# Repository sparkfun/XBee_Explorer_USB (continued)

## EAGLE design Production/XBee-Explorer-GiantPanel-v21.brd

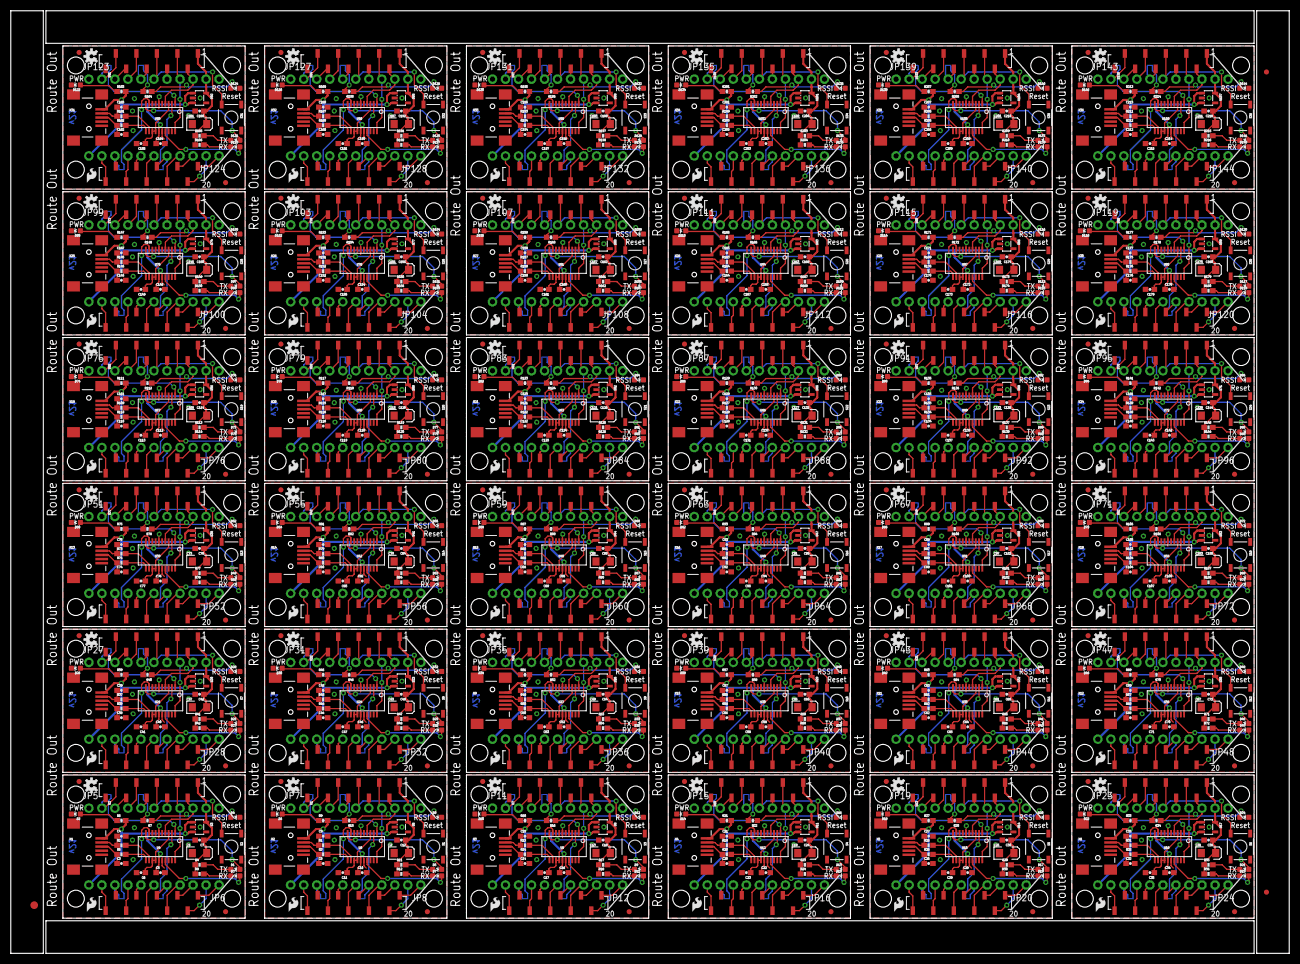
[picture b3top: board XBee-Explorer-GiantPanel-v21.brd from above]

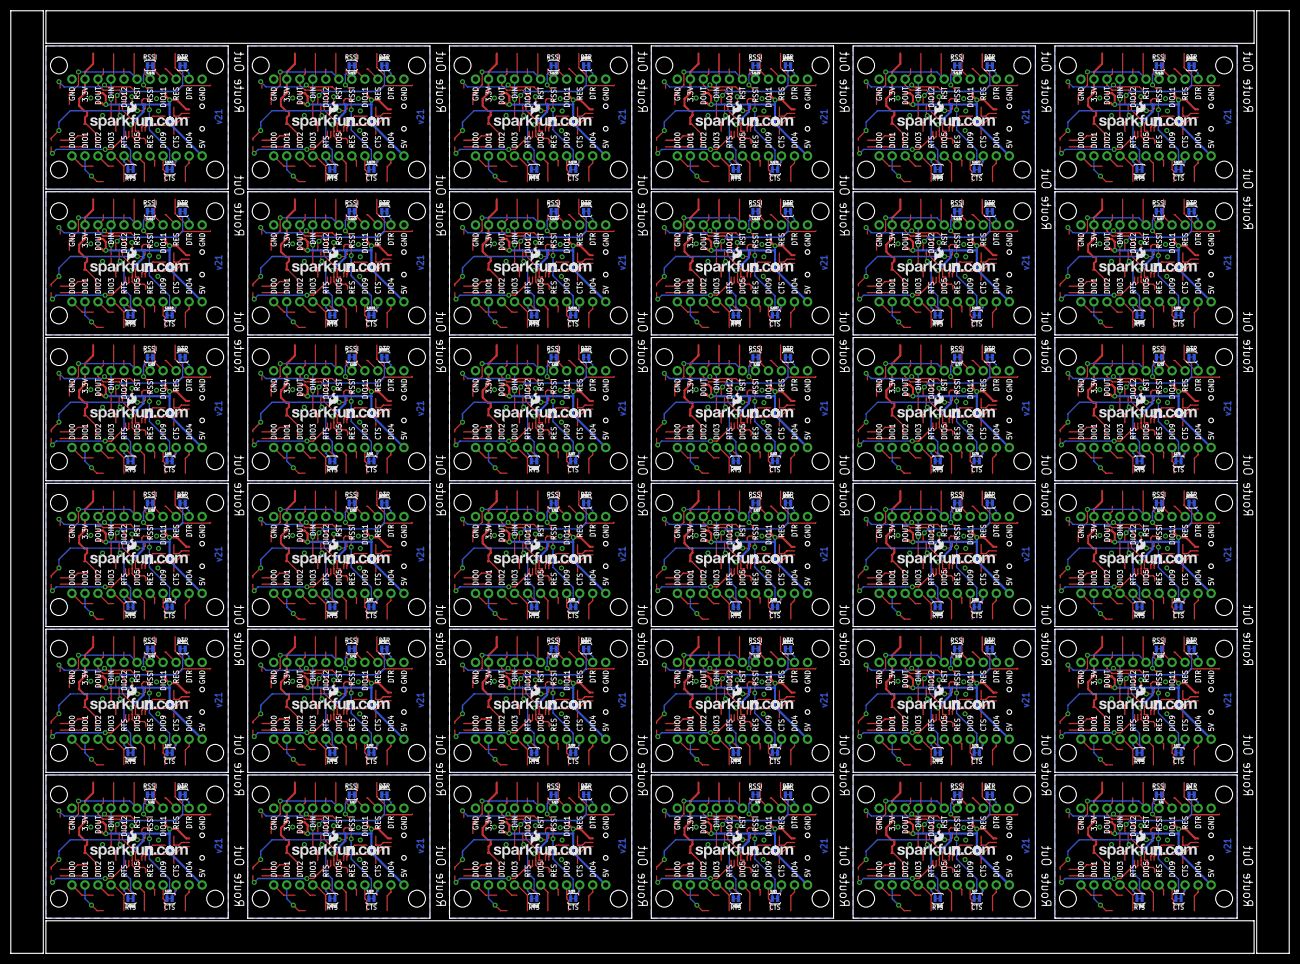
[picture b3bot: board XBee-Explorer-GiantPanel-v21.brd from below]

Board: 2 copper layers, 249.4 x 183.9 mm, 1299 parts (180 on the bottom side), 1296 nets.

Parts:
C1, C2, C13, C19, C25, C31, C37, C43, C49, C55, C61, C67, C73, C79, C85, C91, C97, C103, C109, C115, C121, C127, C133, C139, C145, C151, C157, C163, C169, C175, C181, C187, C193, C199, C205, C211: 10uF; EIA3216
C3, C4, C8, C9, C14, C15, C20, C21, C26, C27, C32, C33, C38, C39, C44, C45, C50, C51, C56, C57, C62, C63, C68, C69, C74, C75, C80, C81, C86, C87, C92, C93, C98, C99, C104, C105, C110, C111, C116, C117, C122, C123, C128, C129, C134, C135, C140, C141, C146, C147, C152, C153, C158, C159, C164, C165, C170, C171, C176, C177, C182, C183, C188, C189, C194, C195, C200, C201, C206, C207, C212, C213: 47pF; 0603-CAP
C5, C6, C7, C10, C11, C12, C16, C17, C18, C22, C23, C24, C28, C29, C30, C34, C35, C36, C40, C41, C42, C46, C47, C48, C52, C53, C54, C58, C59, C60, C64, C65, C66, C70, C71, C72, C76, C77, C78, C82, C83, C84, C88, C89, C90, C94, C95, C96, C100, C101, C102, C106, C107, C108, C112, C113, C114, C118, C119, C120, C124, C125, C126, C130, C131, C132, C136, C137, C138, C142, C143, C144, C148, C149, C150, C154, C155, C156, C160, C161, C162, C166, C167, C168, C172, C173, C174, C178, C179, C180, C184, C185, C186, C190, C191, C192, C196, C197, C198, C202, C203, C204, C208, C209, C210, C214, C215, C216: 0.1uF; 0603-CAP
D1, D2, D5, D6, D9, D10, D13, D14, D17, D18, D21, D22, D25, D26, D29, D30, D33, D34, D37, D38, D41, D42, D45, D46, D49, D50, D53, D54, D57, D58, D61, D62, D65, D66, D69, D70, D73, D74, D77, D78, D81, D82, D85, D86, D89, D90, D93, D94, D97, D98, D101, D102, D105, D106, D109, D110, D113, D114, D117, D118, D121, D122, D125, D126, D129, D130, D133, D134, D137, D138, D141, D142: RED; LED-0603
D3, D4, D7, D8, D11, D12, D15, D16, D19, D20, D23, D24, D27, D28, D31, D32, D35, D36, D39, D40, D43, D44, D47, D48, D51, D52, D55, D56, D59, D60, D63, D64, D67, D68, D71, D72, D75, D76, D79, D80, D83, D84, D87, D88, D91, D92, D95, D96, D99, D100, D103, D104, D107, D108, D111, D112, D115, D116, D119, D120, D123, D124, D127, D128, D131, D132, D135, D136, D139, D140, D143, D144: GREEN; LED-0603
E$1: FIDUCIAL-1.5X3
E$5, E$7: FIDUCIAL-1X2
JP1, JP2, JP3, JP4, JP9, JP10, JP13, JP14, JP17, JP18, JP21, JP22, JP25, JP26, JP29, JP30, JP33, JP34, JP37, JP38, JP41, JP42, JP45, JP46, JP49, JP50, JP53, JP54, JP57, JP58, JP61, JP62, JP65, JP66, JP69, JP70, JP73, JP74, JP77, JP78, JP81, JP82, JP85, JP86, JP89, JP90, JP93, JP94, JP97, JP98, JP101, JP102, JP105, JP106, JP109, JP110, JP113, JP114, JP117, JP118, JP121, JP122, JP125, JP126, JP129, JP130, JP133, JP134, JP137, JP138, JP141, JP142: FIDUCIAL1X2; FIDUCIAL-1X2
JP5, JP6, JP7, JP8, JP11, JP12, JP15, JP16, JP19, JP20, JP23, JP24, JP27, JP28, JP31, JP32, JP35, JP36, JP39, JP40, JP43, JP44, JP47, JP48, JP51, JP52, JP55, JP56, JP59, JP60, JP63, JP64, JP67, JP68, JP71, JP72, JP75, JP76, JP79, JP80, JP83, JP84, JP87, JP88, JP91, JP92, JP95, JP96, JP99, JP100, JP103, JP104, JP107, JP108, JP111, JP112, JP115, JP116, JP119, JP120, JP123, JP124, JP127, JP128, JP131, JP132, JP135, JP136, JP139, JP140, JP143, JP144: M111X11_NO_SILK; 1X11_NO_SILK
LOGO1, LOGO2, LOGO3, LOGO4, LOGO5, LOGO6, LOGO7, LOGO8, LOGO9, LOGO10, LOGO11, LOGO12, LOGO13, LOGO14, LOGO15, LOGO16, LOGO17, LOGO18, LOGO19, LOGO20, LOGO21, LOGO22, LOGO23, LOGO24, LOGO25, LOGO26, LOGO27, LOGO28, LOGO29, LOGO30, LOGO31, LOGO32, LOGO33, LOGO34, LOGO35, LOGO36: OSHW-LOGOS; OSHW-LOGO-S
R1, R2, R3, R5, R13, R14, R19, R20, R25, R26, R31, R32, R37, R38, R43, R44, R49, R50, R55, R56, R61, R62, R67, R68, R73, R74, R79, R80, R85, R86, R91, R92, R97, R98, R103, R104, R109, R110, R115, R116, R121, R122, R127, R128, R133, R134, R139, R140, R145, R146, R151, R152, R157, R158, R163, R164, R169, R170, R175, R176, R181, R182, R187, R188, R193, R194, R199, R200, R205, R206, R211, R212: 27; 0603-RES
R4, R6, R8, R9, R11, R12, R15, R17, R18, R21, R23, R24, R27, R29, R30, R33, R35, R36, R39, R41, R42, R45, R47, R48, R51, R53, R54, R57, R59, R60, R63, R65, R66, R69, R71, R72, R75, R77, R78, R81, R83, R84, R87, R89, R90, R93, R95, R96, R99, R101, R102, R105, R107, R108, R111, R113, R114, R117, R119, R120, R123, R125, R126, R129, R131, R132, R135, R137, R138, R141, R143, R144, R147, R149, R150, R153, R155, R156, R159, R161, R162, R165, R167, R168, R171, R173, R174, R177, R179, R180, R183, R185, R186, R189, R191, R192, R195, R197, R198, R201, R203, R204, R207, R209, R210, R213, R215, R216: 1k; 0603-RES
R7, R10, R16, R22, R28, R34, R40, R46, R52, R58, R64, R70, R76, R82, R88, R94, R100, R106, R112, R118, R124, R130, R136, R142, R148, R154, R160, R166, R172, R178, R184, R190, R196, R202, R208, R214: 330; 0603-RES
S1, S2, S3, S4, S5, S6, S7, S8, S9, S10, S11, S12, S13, S14, S15, S16, S17, S18, S19, S20, S21, S22, S23, S24, S25, S26, S27, S28, S29, S30, S31, S32, S33, S34, S35, S36: Reset; TACTILE_SWITCH_SMD
SJ1, SJ5, SJ9, SJ13, SJ17, SJ21, SJ25, SJ29, SJ33, SJ37, SJ41, SJ45, SJ49, SJ53, SJ57, SJ61, SJ65, SJ69, SJ73, SJ77, SJ81, SJ85, SJ89, SJ93, SJ97, SJ101, SJ105, SJ109, SJ113, SJ117, SJ121, SJ125, SJ129, SJ133, SJ137, SJ141: RSSI_LED_EN; SJ_2S-TRACE
SJ2, SJ8, SJ12, SJ16, SJ20, SJ24, SJ28, SJ32, SJ36, SJ40, SJ44, SJ48, SJ52, SJ56, SJ60, SJ64, SJ68, SJ72, SJ76, SJ80, SJ84, SJ88, SJ92, SJ96, SJ100, SJ104, SJ108, SJ112, SJ116, SJ120, SJ124, SJ128, SJ132, SJ136, SJ140, SJ144: CTS_EN; SJ_2S-TRACE
SJ3, SJ7, SJ11, SJ15, SJ19, SJ23, SJ27, SJ31, SJ35, SJ39, SJ43, SJ47, SJ51, SJ55, SJ59, SJ63, SJ67, SJ71, SJ75, SJ79, SJ83, SJ87, SJ91, SJ95, SJ99, SJ103, SJ107, SJ111, SJ115, SJ119, SJ123, SJ127, SJ131, SJ135, SJ139, SJ143: RTS_EN; SJ_2S-TRACE
SJ4, SJ6, SJ10, SJ14, SJ18, SJ22, SJ26, SJ30, SJ34, SJ38, SJ42, SJ46, SJ50, SJ54, SJ58, SJ62, SJ66, SJ70, SJ74, SJ78, SJ82, SJ86, SJ90, SJ94, SJ98, SJ102, SJ106, SJ110, SJ114, SJ118, SJ122, SJ126, SJ130, SJ134, SJ138, SJ142: DTR; SJ_2S-TRACE
U1, U2, U7, U10, U13, U16, U19, U22, U25, U28, U31, U34, U37, U40, U43, U46, U49, U52, U55, U58, U61, U64, U67, U70, U73, U76, U79, U82, U85, U88, U91, U94, U97, U100, U103, U106: XBEE-1B3; XBEE-SMD
U3, U5, U8, U11, U14, U17, U20, U23, U26, U29, U32, U35, U38, U41, U44, U47, U50, U53, U56, U59, U62, U65, U68, U71, U74, U77, U80, U83, U86, U89, U92, U95, U98, U101, U104, U107: MIC5205 3.3V; SOT23-5
U4, U6, U9, U12, U15, U18, U21, U24, U27, U30, U33, U36, U39, U42, U45, U48, U51, U54, U57, U60, U63, U66, U69, U72, U75, U78, U81, U84, U87, U90, U93, U96, U99, U102, U105, U108: FT231XS; SSOP20_L
U$1, U$2, U$13, U$19, U$25, U$31, U$37, U$43, U$49, U$55, U$61, U$67, U$73, U$79, U$85, U$91, U$97, U$103, U$109, U$115, U$121, U$127, U$133, U$139, U$145, U$151, U$157, U$163, U$169, U$175, U$181, U$187, U$193, U$199, U$205, U$211: LOGO-SFESK; SFE-LOGO-FLAME
U$3, U$4, U$14, U$20, U$26, U$32, U$38, U$44, U$50, U$56, U$62, U$68, U$74, U$80, U$86, U$92, U$98, U$104, U$110, U$116, U$122, U$128, U$134, U$140, U$146, U$152, U$158, U$164, U$170, U$176, U$182, U$188, U$194, U$200, U$206, U$212: LOGO-SFENEW; SFE-NEW-WEBLOGO
U$5, U$6, U$7, U$8, U$9, U$10, U$11, U$12, U$15, U$16, U$17, U$18, U$21, U$22, U$23, U$24, U$27, U$28, U$29, U$30, U$33, U$34, U$35, U$36, U$39, U$40, U$41, U$42, U$45, U$46, U$47, U$48, U$51, U$52, U$53, U$54, U$57, U$58, U$59, U$60, U$63, U$64, U$65, U$66, U$69, U$70, U$71, U$72, U$75, U$76, U$77, U$78, U$81, U$82, U$83, U$84, U$87, U$88, U$89, U$90, U$93, U$94, U$95, U$96, U$99, U$100, U$101, U$102, U$105, U$106, U$107, U$108, U$111, U$112, U$113, U$114, U$117, U$118, U$119, U$120, U$123, U$124, U$125, U$126, U$129, U$130, U$131, U$132, U$135, U$136, U$137, U$138, U$141, U$142, U$143, U$144, U$147, U$148, U$149, U$150, U$153, U$154, U$155, U$156, U$159, U$160, U$161, U$162, U$165, U$166, U$167, U$168, U$171, U$172, U$173, U$174, U$177, U$178, U$179, U$180, U$183, U$184, U$185, U$186, U$189, U$190, U$191, U$192, U$195, U$196, U$197, U$198, U$201, U$202, U$203, U$204, U$207, U$208, U$209, U$210, U$213, U$214, U$215, U$216: STAND-OFF
X1, X2, X3, X4, X5, X6, X7, X8, X9, X10, X11, X12, X13, X14, X15, X16, X17, X18, X19, X20, X21, X22, X23, X24, X25, X26, X27, X28, X29, X30, X31, X32, X33, X34, X35, X36: USBSMD; USB-MINIB

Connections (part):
3.3V: C1.A, C7.1, JP5.10, R4.1, R8.1, U2.1, U3.5
3.3V1: C2.A, C12.1, JP7.10, R11.1, R12.1, U1.1, U5.5
3.3V2: C13.A, C18.1, JP11.10, R17.1, R18.1, U7.1, U8.5
3.3V3: C19.A, C24.1, JP15.10, R23.1, R24.1, U10.1, U11.5
3.3V4: C25.A, C30.1, JP19.10, R29.1, R30.1, U13.1, U14.5
3.3V5: C31.A, C36.1, JP23.10, R35.1, R36.1, U16.1, U17.5
3.3V6: C37.A, C42.1, JP27.10, R41.1, R42.1, U19.1, U20.5
3.3V7: C43.A, C48.1, JP31.10, R47.1, R48.1, U22.1, U23.5
3.3V8: C49.A, C54.1, JP35.10, R53.1, R54.1, U25.1, U26.5
3.3V9: C55.A, C60.1, JP39.10, R59.1, R60.1, U28.1, U29.5
3.3V10: C61.A, C66.1, JP43.10, R65.1, R66.1, U31.1, U32.5
3.3V11: C67.A, C72.1, JP47.10, R71.1, R72.1, U34.1, U35.5
3.3V12: C73.A, C78.1, JP51.10, R77.1, R78.1, U37.1, U38.5
3.3V13: C79.A, C84.1, JP55.10, R83.1, R84.1, U40.1, U41.5
3.3V14: C85.A, C90.1, JP59.10, R89.1, R90.1, U43.1, U44.5
3.3V15: C91.A, C96.1, JP63.10, R95.1, R96.1, U46.1, U47.5
3.3V16: C97.A, C102.1, JP67.10, R101.1, R102.1, U49.1, U50.5
3.3V17: C103.A, C108.1, JP71.10, R107.1, R108.1, U52.1, U53.5
3.3V18: C109.A, C114.1, JP75.10, R113.1, R114.1, U55.1, U56.5
3.3V19: C115.A, C120.1, JP79.10, R119.1, R120.1, U58.1, U59.5
3.3V20: C121.A, C126.1, JP83.10, R125.1, R126.1, U61.1, U62.5
3.3V21: C127.A, C132.1, JP87.10, R131.1, R132.1, U64.1, U65.5
3.3V22: C133.A, C138.1, JP91.10, R137.1, R138.1, U67.1, U68.5
3.3V23: C139.A, C144.1, JP95.10, R143.1, R144.1, U70.1, U71.5
3.3V24: C145.A, C150.1, JP99.10, R149.1, R150.1, U73.1, U74.5
3.3V25: C151.A, C156.1, JP103.10, R155.1, R156.1, U76.1, U77.5
3.3V26: C157.A, C162.1, JP107.10, R161.1, R162.1, U79.1, U80.5
3.3V27: C163.A, C168.1, JP111.10, R167.1, R168.1, U82.1, U83.5
3.3V28: C169.A, C174.1, JP115.10, R173.1, R174.1, U85.1, U86.5
3.3V29: C175.A, C180.1, JP119.10, R179.1, R180.1, U88.1, U89.5
3.3V30: C181.A, C186.1, JP123.10, R185.1, R186.1, U91.1, U92.5
3.3V31: C187.A, C192.1, JP127.10, R191.1, R192.1, U94.1, U95.5
3.3V32: C193.A, C198.1, JP131.10, R197.1, R198.1, U97.1, U98.5
3.3V33: C199.A, C204.1, JP135.10, R203.1, R204.1, U100.1, U101.5
3.3V34: C205.A, C210.1, JP139.10, R209.1, R210.1, U103.1, U104.5
3.3V35: C211.A, C216.1, JP143.10, R215.1, R216.1, U106.1, U107.5
3V-INT: C6.1, U4.3, U4.13, U4.14
3V-INT1: C11.1, U6.3, U6.13, U6.14
3V-INT2: C17.1, U9.3, U9.13, U9.14
3V-INT3: C23.1, U12.3, U12.13, U12.14
3V-INT4: C29.1, U15.3, U15.13, U15.14
3V-INT5: C35.1, U18.3, U18.13, U18.14
3V-INT6: C41.1, U21.3, U21.13, U21.14
3V-INT7: C47.1, U24.3, U24.13, U24.14
3V-INT8: C53.1, U27.3, U27.13, U27.14
3V-INT9: C59.1, U30.3, U30.13, U30.14
3V-INT10: C65.1, U33.3, U33.13, U33.14
3V-INT11: C71.1, U36.3, U36.13, U36.14
3V-INT12: C77.1, U39.3, U39.13, U39.14
3V-INT13: C83.1, U42.3, U42.13, U42.14
3V-INT14: C89.1, U45.3, U45.13, U45.14
3V-INT15: C95.1, U48.3, U48.13, U48.14
3V-INT16: C101.1, U51.3, U51.13, U51.14
3V-INT17: C107.1, U54.3, U54.13, U54.14
3V-INT18: C113.1, U57.3, U57.13, U57.14
3V-INT19: C119.1, U60.3, U60.13, U60.14
3V-INT20: C125.1, U63.3, U63.13, U63.14
3V-INT21: C131.1, U66.3, U66.13, U66.14
3V-INT22: C137.1, U69.3, U69.13, U69.14
3V-INT23: C143.1, U72.3, U72.13, U72.14
3V-INT24: C149.1, U75.3, U75.13, U75.14
3V-INT25: C155.1, U78.3, U78.13, U78.14
3V-INT26: C161.1, U81.3, U81.13, U81.14
3V-INT27: C167.1, U84.3, U84.13, U84.14
3V-INT28: C173.1, U87.3, U87.13, U87.14
3V-INT29: C179.1, U90.3, U90.13, U90.14
3V-INT30: C185.1, U93.3, U93.13, U93.14
3V-INT31: C191.1, U96.3, U96.13, U96.14
3V-INT32: C197.1, U99.3, U99.13, U99.14
3V-INT33: C203.1, U102.3, U102.13, U102.14
3V-INT34: C209.1, U105.3, U105.13, U105.14
3V-INT35: C215.1, U108.3, U108.13, U108.14
5V: C5.1, JP6.11, R6.2, U3.1, U3.3, U4.15, X1.VBUS
5V1: C10.1, JP8.11, R9.2, U5.1, U5.3, U6.15, X2.VBUS
5V2: C16.1, JP12.11, R15.2, U8.1, U8.3, U9.15, X3.VBUS
5V3: C22.1, JP16.11, R21.2, U11.1, U11.3, U12.15, X4.VBUS
5V4: C28.1, JP20.11, R27.2, U14.1, U14.3, U15.15, X5.VBUS
5V5: C34.1, JP24.11, R33.2, U17.1, U17.3, U18.15, X6.VBUS
5V6: C40.1, JP28.11, R39.2, U20.1, U20.3, U21.15, X7.VBUS
5V7: C46.1, JP32.11, R45.2, U23.1, U23.3, U24.15, X8.VBUS
5V8: C52.1, JP36.11, R51.2, U26.1, U26.3, U27.15, X9.VBUS
5V9: C58.1, JP40.11, R57.2, U29.1, U29.3, U30.15, X10.VBUS
5V10: C64.1, JP44.11, R63.2, U32.1, U32.3, U33.15, X11.VBUS
5V11: C70.1, JP48.11, R69.2, U35.1, U35.3, U36.15, X12.VBUS
5V12: C76.1, JP52.11, R75.2, U38.1, U38.3, U39.15, X13.VBUS
5V13: C82.1, JP56.11, R81.2, U41.1, U41.3, U42.15, X14.VBUS
5V14: C88.1, JP60.11, R87.2, U44.1, U44.3, U45.15, X15.VBUS
5V15: C94.1, JP64.11, R93.2, U47.1, U47.3, U48.15, X16.VBUS
5V16: C100.1, JP68.11, R99.2, U50.1, U50.3, U51.15, X17.VBUS
5V17: C106.1, JP72.11, R105.2, U53.1, U53.3, U54.15, X18.VBUS
5V18: C112.1, JP76.11, R111.2, U56.1, U56.3, U57.15, X19.VBUS
5V19: C118.1, JP80.11, R117.2, U59.1, U59.3, U60.15, X20.VBUS
5V20: C124.1, JP84.11, R123.2, U62.1, U62.3, U63.15, X21.VBUS
5V21: C130.1, JP88.11, R129.2, U65.1, U65.3, U66.15, X22.VBUS
5V22: C136.1, JP92.11, R135.2, U68.1, U68.3, U69.15, X23.VBUS
5V23: C142.1, JP96.11, R141.2, U71.1, U71.3, U72.15, X24.VBUS
5V24: C148.1, JP100.11, R147.2, U74.1, U74.3, U75.15, X25.VBUS
5V25: C154.1, JP104.11, R153.2, U77.1, U77.3, U78.15, X26.VBUS
5V26: C160.1, JP108.11, R159.2, U80.1, U80.3, U81.15, X27.VBUS
5V27: C166.1, JP112.11, R165.2, U83.1, U83.3, U84.15, X28.VBUS
5V28: C172.1, JP116.11, R171.2, U86.1, U86.3, U87.15, X29.VBUS
5V29: C178.1, JP120.11, R177.2, U89.1, U89.3, U90.15, X30.VBUS
5V30: C184.1, JP124.11, R183.2, U92.1, U92.3, U93.15, X31.VBUS
5V31: C190.1, JP128.11, R189.2, U95.1, U95.3, U96.15, X32.VBUS
5V32: C196.1, JP132.11, R195.2, U98.1, U98.3, U99.15, X33.VBUS
5V33: C202.1, JP136.11, R201.2, U101.1, U101.3, U102.15, X34.VBUS
5V34: C208.1, JP140.11, R207.2, U104.1, U104.3, U105.15, X35.VBUS
5V35: C214.1, JP144.11, R213.2, U107.1, U107.3, U108.15, X36.VBUS
CTS: SJ3.1, U4.9
CTS1: SJ7.1, U6.9
CTS2: SJ11.1, U9.9
CTS3: SJ15.1, U12.9
CTS4: SJ19.1, U15.9
CTS5: SJ23.1, U18.9
CTS6: SJ27.1, U21.9
CTS7: SJ31.1, U24.9
CTS8: SJ35.1, U27.9
CTS9: SJ39.1, U30.9
CTS10: SJ43.1, U33.9
CTS11: SJ47.1, U36.9
CTS12: SJ51.1, U39.9
CTS13: SJ55.1, U42.9
CTS14: SJ59.1, U45.9
CTS15: SJ63.1, U48.9
CTS16: SJ67.1, U51.9
CTS17: SJ71.1, U54.9
CTS18: SJ75.1, U57.9
CTS19: SJ79.1, U60.9
CTS20: SJ83.1, U63.9
CTS21: SJ87.1, U66.9
CTS22: SJ91.1, U69.9
CTS23: SJ95.1, U72.9
CTS24: SJ99.1, U75.9
CTS25: SJ103.1, U78.9
CTS26: SJ107.1, U81.9
CTS27: SJ111.1, U84.9
CTS28: SJ115.1, U87.9
CTS29: SJ119.1, U90.9
CTS30: SJ123.1, U93.9
CTS31: SJ127.1, U96.9
CTS32: SJ131.1, U99.9
CTS33: SJ135.1, U102.9
CTS34: SJ139.1, U105.9
CTS35: SJ143.1, U108.9
CTS_XBEE: JP6.9, SJ3.2, U2.12
CTS_XBEE1: JP8.9, SJ7.2, U1.12
CTS_XBEE2: JP12.9, SJ11.2, U7.12
CTS_XBEE3: JP16.9, SJ15.2, U10.12
CTS_XBEE4: JP20.9, SJ19.2, U13.12
CTS_XBEE5: JP24.9, SJ23.2, U16.12
CTS_XBEE6: JP28.9, SJ27.2, U19.12
CTS_XBEE7: JP32.9, SJ31.2, U22.12
CTS_XBEE8: JP36.9, SJ35.2, U25.12
CTS_XBEE9: JP40.9, SJ39.2, U28.12
CTS_XBEE10: JP44.9, SJ43.2, U31.12
CTS_XBEE11: JP48.9, SJ47.2, U34.12
CTS_XBEE12: JP52.9, SJ51.2, U37.12
CTS_XBEE13: JP56.9, SJ55.2, U40.12
CTS_XBEE14: JP60.9, SJ59.2, U43.12
CTS_XBEE15: JP64.9, SJ63.2, U46.12
CTS_XBEE16: JP68.9, SJ67.2, U49.12
CTS_XBEE17: JP72.9, SJ71.2, U52.12
CTS_XBEE18: JP76.9, SJ75.2, U55.12
CTS_XBEE19: JP80.9, SJ79.2, U58.12
CTS_XBEE20: JP84.9, SJ83.2, U61.12
CTS_XBEE21: JP88.9, SJ87.2, U64.12
CTS_XBEE22: JP92.9, SJ91.2, U67.12
CTS_XBEE23: JP96.9, SJ95.2, U70.12
CTS_XBEE24: JP100.9, SJ99.2, U73.12
CTS_XBEE25: JP104.9, SJ103.2, U76.12
CTS_XBEE26: JP108.9, SJ107.2, U79.12
CTS_XBEE27: JP112.9, SJ111.2, U82.12
CTS_XBEE28: JP116.9, SJ115.2, U85.12
CTS_XBEE29: JP120.9, SJ119.2, U88.12
CTS_XBEE30: JP124.9, SJ123.2, U91.12
CTS_XBEE31: JP128.9, SJ127.2, U94.12
CTS_XBEE32: JP132.9, SJ131.2, U97.12
CTS_XBEE33: JP136.9, SJ135.2, U100.12
CTS_XBEE34: JP140.9, SJ139.2, U103.12
CTS_XBEE35: JP144.9, SJ143.2, U106.12
DIN: JP5.8, U2.3, U4.20
DIN1: JP7.8, U1.3, U6.20
DIN2: JP11.8, U7.3, U9.20
DIN3: JP15.8, U10.3, U12.20
DIN4: JP19.8, U13.3, U15.20
DIN5: JP23.8, U16.3, U18.20
DIN6: JP27.8, U19.3, U21.20
DIN7: JP31.8, U22.3, U24.20
DIN8: JP35.8, U25.3, U27.20
DIN9: JP39.8, U28.3, U30.20
DIN10: JP43.8, U31.3, U33.20
DIN11: JP47.8, U34.3, U36.20
DIN12: JP51.8, U37.3, U39.20
DIN13: JP55.8, U40.3, U42.20
DIN14: JP59.8, U43.3, U45.20
DIN15: JP63.8, U46.3, U48.20
DIN16: JP67.8, U49.3, U51.20
DIN17: JP71.8, U52.3, U54.20
DIN18: JP75.8, U55.3, U57.20
DIN19: JP79.8, U58.3, U60.20
DIN20: JP83.8, U61.3, U63.20
DIN21: JP87.8, U64.3, U66.20
DIN22: JP91.8, U67.3, U69.20
DIN23: JP95.8, U70.3, U72.20
DIN24: JP99.8, U73.3, U75.20
DIN25: JP103.8, U76.3, U78.20
DIN26: JP107.8, U79.3, U81.20
DIN27: JP111.8, U82.3, U84.20
DIN28: JP115.8, U85.3, U87.20
DIN29: JP119.8, U88.3, U90.20
DIN30: JP123.8, U91.3, U93.20
DIN31: JP127.8, U94.3, U96.20
DIN32: JP131.8, U97.3, U99.20
DIN33: JP135.8, U100.3, U102.20
DIN34: JP139.8, U103.3, U105.20
DIN35: JP143.8, U106.3, U108.20
DIO0: JP6.1, U2.20
DIO1: JP6.2, U2.19
DIO2: JP6.3, U2.18
DIO3: JP6.4, U2.17
DIO4: JP6.10, U2.11
DIO5: JP6.6, U2.15
DIO6: JP8.10, U1.11
DIO7: JP8.8, U1.13
DIO8: JP8.6, U1.15
DIO9: JP6.8, U2.13
DIO10: JP8.4, U1.17
DIO11: JP5.4, U2.7
DIO12: JP5.7, U2.4
DIO13: JP8.3, U1.18
DIO14: JP8.2, U1.19
DIO15: JP8.1, U1.20
DIO16: JP7.4, U1.7
DIO17: JP7.7, U1.4
DIO18: JP12.10, U7.11
DIO19: JP12.8, U7.13
DIO20: JP12.6, U7.15
DIO21: JP12.4, U7.17
DIO22: JP12.3, U7.18
DIO23: JP12.2, U7.19
DIO24: JP12.1, U7.20
DIO25: JP11.4, U7.7
DIO26: JP11.7, U7.4
DIO27: JP16.10, U10.11
DIO28: JP16.8, U10.13
DIO29: JP16.6, U10.15
DIO30: JP16.4, U10.17
DIO31: JP16.3, U10.18
DIO32: JP16.2, U10.19
DIO33: JP16.1, U10.20
DIO34: JP15.4, U10.7
DIO35: JP15.7, U10.4
DIO36: JP20.10, U13.11
DIO37: JP20.8, U13.13
DIO38: JP20.6, U13.15
DIO39: JP20.4, U13.17
DIO40: JP20.3, U13.18
DIO41: JP20.2, U13.19
DIO42: JP20.1, U13.20
DIO43: JP19.4, U13.7
DIO44: JP19.7, U13.4
DIO45: JP24.10, U16.11
DIO46: JP24.8, U16.13
DIO47: JP24.6, U16.15
DIO48: JP24.4, U16.17
DIO49: JP24.3, U16.18
DIO50: JP24.2, U16.19
DIO51: JP24.1, U16.20
DIO52: JP23.4, U16.7
DIO53: JP23.7, U16.4
DIO54: JP28.10, U19.11
DIO55: JP28.8, U19.13
DIO56: JP28.6, U19.15
DIO57: JP28.4, U19.17
DIO58: JP28.3, U19.18
DIO59: JP28.2, U19.19
DIO60: JP28.1, U19.20
DIO61: JP27.4, U19.7
DIO62: JP27.7, U19.4
DIO63: JP32.10, U22.11
DIO64: JP32.8, U22.13
DIO65: JP32.6, U22.15
DIO66: JP32.4, U22.17
DIO67: JP32.3, U22.18
DIO68: JP32.2, U22.19
DIO69: JP32.1, U22.20
DIO70: JP31.4, U22.7
DIO71: JP31.7, U22.4
DIO72: JP36.10, U25.11
DIO73: JP36.8, U25.13
DIO74: JP36.6, U25.15
DIO75: JP36.4, U25.17
DIO76: JP36.3, U25.18
DIO77: JP36.2, U25.19
DIO78: JP36.1, U25.20
DIO79: JP35.4, U25.7
DIO80: JP35.7, U25.4
DIO81: JP40.10, U28.11
DIO82: JP40.8, U28.13
DIO83: JP40.6, U28.15
DIO84: JP40.4, U28.17
DIO85: JP40.3, U28.18
DIO86: JP40.2, U28.19
DIO87: JP40.1, U28.20
DIO88: JP39.4, U28.7
DIO89: JP39.7, U28.4
DIO90: JP44.10, U31.11
DIO91: JP44.8, U31.13
DIO92: JP44.6, U31.15
DIO93: JP44.4, U31.17
DIO94: JP44.3, U31.18
DIO95: JP44.2, U31.19
DIO96: JP44.1, U31.20
DIO97: JP43.4, U31.7
DIO98: JP43.7, U31.4
DIO99: JP48.10, U34.11
DIO100: JP48.8, U34.13
DIO101: JP48.6, U34.15
DIO102: JP48.4, U34.17
DIO103: JP48.3, U34.18
DIO104: JP48.2, U34.19
DIO105: JP48.1, U34.20
DIO106: JP47.4, U34.7
DIO107: JP47.7, U34.4
DIO108: JP52.10, U37.11
DIO109: JP52.8, U37.13
DIO110: JP52.6, U37.15
DIO111: JP52.4, U37.17
DIO112: JP52.3, U37.18
DIO113: JP52.2, U37.19
DIO114: JP52.1, U37.20
DIO115: JP51.4, U37.7
DIO116: JP51.7, U37.4
DIO117: JP56.10, U40.11
DIO118: JP56.8, U40.13
DIO119: JP56.6, U40.15
DIO120: JP56.4, U40.17
DIO121: JP56.3, U40.18
DIO122: JP56.2, U40.19
DIO123: JP56.1, U40.20
DIO124: JP55.4, U40.7
DIO125: JP55.7, U40.4
DIO126: JP60.10, U43.11
DIO127: JP60.8, U43.13
DIO128: JP60.6, U43.15
DIO129: JP60.4, U43.17
DIO130: JP60.3, U43.18
DIO131: JP60.2, U43.19
DIO132: JP60.1, U43.20
DIO133: JP59.4, U43.7
DIO134: JP59.7, U43.4
DIO135: JP64.10, U46.11
DIO136: JP64.8, U46.13
DIO137: JP64.6, U46.15
DIO138: JP64.4, U46.17
DIO139: JP64.3, U46.18
DIO140: JP64.2, U46.19
DIO141: JP64.1, U46.20
DIO142: JP63.4, U46.7
DIO143: JP63.7, U46.4
DIO144: JP68.10, U49.11
DIO145: JP68.8, U49.13
DIO146: JP68.6, U49.15
DIO147: JP68.4, U49.17
DIO148: JP68.3, U49.18
DIO149: JP68.2, U49.19
DIO150: JP68.1, U49.20
DIO151: JP67.4, U49.7
DIO152: JP67.7, U49.4
DIO153: JP72.10, U52.11
DIO154: JP72.8, U52.13
DIO155: JP72.6, U52.15
DIO156: JP72.4, U52.17
DIO157: JP72.3, U52.18
DIO158: JP72.2, U52.19
DIO159: JP72.1, U52.20
DIO160: JP71.4, U52.7
DIO161: JP71.7, U52.4
DIO162: JP76.10, U55.11
DIO163: JP76.8, U55.13
DIO164: JP76.6, U55.15
DIO165: JP76.4, U55.17
DIO166: JP76.3, U55.18
DIO167: JP76.2, U55.19
DIO168: JP76.1, U55.20
DIO169: JP75.4, U55.7
DIO170: JP75.7, U55.4
DIO171: JP80.10, U58.11
DIO172: JP80.8, U58.13
DIO173: JP80.6, U58.15
DIO174: JP80.4, U58.17
DIO175: JP80.3, U58.18
DIO176: JP80.2, U58.19
DIO177: JP80.1, U58.20
DIO178: JP79.4, U58.7
DIO179: JP79.7, U58.4
DIO180: JP84.10, U61.11
DIO181: JP84.8, U61.13
DIO182: JP84.6, U61.15
DIO183: JP84.4, U61.17
DIO184: JP84.3, U61.18
DIO185: JP84.2, U61.19
DIO186: JP84.1, U61.20
DIO187: JP83.4, U61.7
DIO188: JP83.7, U61.4
DIO189: JP88.10, U64.11
DIO190: JP88.8, U64.13
DIO191: JP88.6, U64.15
DIO192: JP88.4, U64.17
DIO193: JP88.3, U64.18
DIO194: JP88.2, U64.19
DIO195: JP88.1, U64.20
DIO196: JP87.4, U64.7
DIO197: JP87.7, U64.4
DIO198: JP92.10, U67.11
DIO199: JP92.8, U67.13
DIO200: JP92.6, U67.15
DIO201: JP92.4, U67.17
DIO202: JP92.3, U67.18
DIO203: JP92.2, U67.19
DIO204: JP92.1, U67.20
DIO205: JP91.4, U67.7
DIO206: JP91.7, U67.4
DIO207: JP96.10, U70.11
DIO208: JP96.8, U70.13
DIO209: JP96.6, U70.15
DIO210: JP96.4, U70.17
DIO211: JP96.3, U70.18
DIO212: JP96.2, U70.19
DIO213: JP96.1, U70.20
DIO214: JP95.4, U70.7
DIO215: JP95.7, U70.4
DIO216: JP100.10, U73.11
DIO217: JP100.8, U73.13
DIO218: JP100.6, U73.15
DIO219: JP100.4, U73.17
DIO220: JP100.3, U73.18
DIO221: JP100.2, U73.19
DIO222: JP100.1, U73.20
DIO223: JP99.4, U73.7
DIO224: JP99.7, U73.4
DIO225: JP104.10, U76.11
DIO226: JP104.8, U76.13
DIO227: JP104.6, U76.15
DIO228: JP104.4, U76.17
DIO229: JP104.3, U76.18
DIO230: JP104.2, U76.19
DIO231: JP104.1, U76.20
DIO232: JP103.4, U76.7
DIO233: JP103.7, U76.4
DIO234: JP108.10, U79.11
DIO235: JP108.8, U79.13
DIO236: JP108.6, U79.15
DIO237: JP108.4, U79.17
DIO238: JP108.3, U79.18
DIO239: JP108.2, U79.19
DIO240: JP108.1, U79.20
DIO241: JP107.4, U79.7
DIO242: JP107.7, U79.4
DIO243: JP112.10, U82.11
DIO244: JP112.8, U82.13
DIO245: JP112.6, U82.15
DIO246: JP112.4, U82.17
DIO247: JP112.3, U82.18
DIO248: JP112.2, U82.19
DIO249: JP112.1, U82.20
DIO250: JP111.4, U82.7
DIO251: JP111.7, U82.4
DIO252: JP116.10, U85.11
DIO253: JP116.8, U85.13
DIO254: JP116.6, U85.15
DIO255: JP116.4, U85.17
DIO256: JP116.3, U85.18
DIO257: JP116.2, U85.19
DIO258: JP116.1, U85.20
DIO259: JP115.4, U85.7
DIO260: JP115.7, U85.4
DIO261: JP120.10, U88.11
DIO262: JP120.8, U88.13
DIO263: JP120.6, U88.15
DIO264: JP120.4, U88.17
DIO265: JP120.3, U88.18
DIO266: JP120.2, U88.19
DIO267: JP120.1, U88.20
DIO268: JP119.4, U88.7
DIO269: JP119.7, U88.4
DIO270: JP124.10, U91.11
DIO271: JP124.8, U91.13
DIO272: JP124.6, U91.15
DIO273: JP124.4, U91.17
DIO274: JP124.3, U91.18
DIO275: JP124.2, U91.19
DIO276: JP124.1, U91.20
DIO277: JP123.4, U91.7
DIO278: JP123.7, U91.4
DIO279: JP128.10, U94.11
DIO280: JP128.8, U94.13
DIO281: JP128.6, U94.15
DIO282: JP128.4, U94.17
DIO283: JP128.3, U94.18
DIO284: JP128.2, U94.19
DIO285: JP128.1, U94.20
DIO286: JP127.4, U94.7
DIO287: JP127.7, U94.4
DIO288: JP132.10, U97.11
DIO289: JP132.8, U97.13
DIO290: JP132.6, U97.15
DIO291: JP132.4, U97.17
DIO292: JP132.3, U97.18
DIO293: JP132.2, U97.19
DIO294: JP132.1, U97.20
DIO295: JP131.4, U97.7
DIO296: JP131.7, U97.4
DIO297: JP136.10, U100.11
DIO298: JP136.8, U100.13
DIO299: JP136.6, U100.15
DIO300: JP136.4, U100.17
DIO301: JP136.3, U100.18
DIO302: JP136.2, U100.19
DIO303: JP136.1, U100.20
DIO304: JP135.4, U100.7
DIO305: JP135.7, U100.4
DIO306: JP140.10, U103.11
DIO307: JP140.8, U103.13
DIO308: JP140.6, U103.15
DIO309: JP140.4, U103.17
DIO310: JP140.3, U103.18
DIO311: JP140.2, U103.19
DIO312: JP140.1, U103.20
DIO313: JP139.4, U103.7
DIO314: JP139.7, U103.4
DIO315: JP144.10, U106.11
DIO316: JP144.8, U106.13
DIO317: JP144.6, U106.15
DIO318: JP144.4, U106.17
DIO319: JP144.3, U106.18
DIO320: JP144.2, U106.19
DIO321: JP144.1, U106.20
DIO322: JP143.4, U106.7
DIO323: JP143.7, U106.4
DOUT: JP5.9, U2.2, U4.4
DOUT1: JP7.9, U1.2, U6.4
DOUT2: JP11.9, U7.2, U9.4
DOUT3: JP15.9, U10.2, U12.4
DOUT4: JP19.9, U13.2, U15.4
DOUT5: JP23.9, U16.2, U18.4
DOUT6: JP27.9, U19.2, U21.4
DOUT7: JP31.9, U22.2, U24.4
DOUT8: JP35.9, U25.2, U27.4
DOUT9: JP39.9, U28.2, U30.4
DOUT10: JP43.9, U31.2, U33.4
DOUT11: JP47.9, U34.2, U36.4
DOUT12: JP51.9, U37.2, U39.4
DOUT13: JP55.9, U40.2, U42.4
DOUT14: JP59.9, U43.2, U45.4
DOUT15: JP63.9, U46.2, U48.4
DOUT16: JP67.9, U49.2, U51.4
DOUT17: JP71.9, U52.2, U54.4
DOUT18: JP75.9, U55.2, U57.4
DOUT19: JP79.9, U58.2, U60.4
DOUT20: JP83.9, U61.2, U63.4
DOUT21: JP87.9, U64.2, U66.4
DOUT22: JP91.9, U67.2, U69.4
DOUT23: JP95.9, U70.2, U72.4
DOUT24: JP99.9, U73.2, U75.4
DOUT25: JP103.9, U76.2, U78.4
DOUT26: JP107.9, U79.2, U81.4
DOUT27: JP111.9, U82.2, U84.4
DOUT28: JP115.9, U85.2, U87.4
DOUT29: JP119.9, U88.2, U90.4
DOUT30: JP123.9, U91.2, U93.4
DOUT31: JP127.9, U94.2, U96.4
DOUT32: JP131.9, U97.2, U99.4
DOUT33: JP135.9, U100.2, U102.4
DOUT34: JP139.9, U103.2, U105.4
DOUT35: JP143.9, U106.2, U108.4
DTR: SJ4.1, U4.1
DTR1: SJ6.1, U6.1
DTR2: SJ10.1, U9.1
DTR3: SJ14.1, U12.1
DTR4: SJ18.1, U15.1
DTR5: SJ22.1, U18.1
DTR6: SJ26.1, U21.1
DTR7: SJ30.1, U24.1
DTR8: SJ34.1, U27.1
DTR9: SJ38.1, U30.1
DTR10: SJ42.1, U33.1
DTR11: SJ46.1, U36.1
DTR12: SJ50.1, U39.1
DTR13: SJ54.1, U42.1
DTR14: SJ58.1, U45.1
DTR15: SJ62.1, U48.1
DTR16: SJ66.1, U51.1
DTR17: SJ70.1, U54.1
DTR18: SJ74.1, U57.1
DTR19: SJ78.1, U60.1
DTR20: SJ82.1, U63.1
DTR21: SJ86.1, U66.1
DTR22: SJ90.1, U69.1
DTR23: SJ94.1, U72.1
DTR24: SJ98.1, U75.1
DTR25: SJ102.1, U78.1
DTR26: SJ106.1, U81.1
DTR27: SJ110.1, U84.1
DTR28: SJ114.1, U87.1
DTR29: SJ118.1, U90.1
DTR30: SJ122.1, U93.1
DTR31: SJ126.1, U96.1
DTR32: SJ130.1, U99.1
DTR33: SJ134.1, U102.1
DTR34: SJ138.1, U105.1
DTR35: SJ142.1, U108.1
DTR_XBEE: JP5.2, SJ4.2, U2.9
DTR_XBEE1: JP7.2, SJ6.2, U1.9
DTR_XBEE2: JP11.2, SJ10.2, U7.9
DTR_XBEE3: JP15.2, SJ14.2, U10.9
DTR_XBEE4: JP19.2, SJ18.2, U13.9
DTR_XBEE5: JP23.2, SJ22.2, U16.9
DTR_XBEE6: JP27.2, SJ26.2, U19.9
DTR_XBEE7: JP31.2, SJ30.2, U22.9
DTR_XBEE8: JP35.2, SJ34.2, U25.9
DTR_XBEE9: JP39.2, SJ38.2, U28.9
DTR_XBEE10: JP43.2, SJ42.2, U31.9
DTR_XBEE11: JP47.2, SJ46.2, U34.9
DTR_XBEE12: JP51.2, SJ50.2, U37.9
DTR_XBEE13: JP55.2, SJ54.2, U40.9
DTR_XBEE14: JP59.2, SJ58.2, U43.9
DTR_XBEE15: JP63.2, SJ62.2, U46.9
DTR_XBEE16: JP67.2, SJ66.2, U49.9
DTR_XBEE17: JP71.2, SJ70.2, U52.9
DTR_XBEE18: JP75.2, SJ74.2, U55.9
DTR_XBEE19: JP79.2, SJ78.2, U58.9
DTR_XBEE20: JP83.2, SJ82.2, U61.9
DTR_XBEE21: JP87.2, SJ86.2, U64.9
DTR_XBEE22: JP91.2, SJ90.2, U67.9
DTR_XBEE23: JP95.2, SJ94.2, U70.9
DTR_XBEE24: JP99.2, SJ98.2, U73.9
DTR_XBEE25: JP103.2, SJ102.2, U76.9
DTR_XBEE26: JP107.2, SJ106.2, U79.9
DTR_XBEE27: JP111.2, SJ110.2, U82.9
DTR_XBEE28: JP115.2, SJ114.2, U85.9
DTR_XBEE29: JP119.2, SJ118.2, U88.9
DTR_XBEE30: JP123.2, SJ122.2, U91.9
DTR_XBEE31: JP127.2, SJ126.2, U94.9
DTR_XBEE32: JP131.2, SJ130.2, U97.9
DTR_XBEE33: JP135.2, SJ134.2, U100.9
DTR_XBEE34: JP139.2, SJ138.2, U103.9
DTR_XBEE35: JP143.2, SJ142.2, U106.9
GND: C1.C, C3.2, C4.2, C5.2, C6.2, C7.2, D2.C, D4.C, JP5.1, JP5.11, S2.1, U2.10, U3.2, U4.6, U4.16, X1.GND
GND1: C2.C, C8.2, C9.2, C10.2, C11.2, C12.2, D6.C, D8.C, JP7.1, JP7.11, S1.1, U1.10, U5.2, U6.6, U6.16, X2.GND
GND2: C13.C, C14.2, C15.2, C16.2, C17.2, C18.2, D10.C, D12.C, JP11.1, JP11.11, S3.1, U7.10, U8.2, U9.6, U9.16, X3.GND
GND3: C19.C, C20.2, C21.2, C22.2, C23.2, C24.2, D14.C, D16.C, JP15.1, JP15.11, S4.1, U10.10, U11.2, U12.6, U12.16, X4.GND
GND4: C25.C, C26.2, C27.2, C28.2, C29.2, C30.2, D18.C, D20.C, JP19.1, JP19.11, S5.1, U13.10, U14.2, U15.6, U15.16, X5.GND
GND5: C31.C, C32.2, C33.2, C34.2, C35.2, C36.2, D22.C, D24.C, JP23.1, JP23.11, S6.1, U16.10, U17.2, U18.6, U18.16, X6.GND
GND6: C37.C, C38.2, C39.2, C40.2, C41.2, C42.2, D26.C, D28.C, JP27.1, JP27.11, S7.1, U19.10, U20.2, U21.6, U21.16, X7.GND
GND7: C43.C, C44.2, C45.2, C46.2, C47.2, C48.2, D30.C, D32.C, JP31.1, JP31.11, S8.1, U22.10, U23.2, U24.6, U24.16, X8.GND
GND8: C49.C, C50.2, C51.2, C52.2, C53.2, C54.2, D34.C, D36.C, JP35.1, JP35.11, S9.1, U25.10, U26.2, U27.6, U27.16, X9.GND
GND9: C55.C, C56.2, C57.2, C58.2, C59.2, C60.2, D38.C, D40.C, JP39.1, JP39.11, S10.1, U28.10, U29.2, U30.6, U30.16, X10.GND
GND10: C61.C, C62.2, C63.2, C64.2, C65.2, C66.2, D42.C, D44.C, JP43.1, JP43.11, S11.1, U31.10, U32.2, U33.6, U33.16, X11.GND
GND11: C67.C, C68.2, C69.2, C70.2, C71.2, C72.2, D46.C, D48.C, JP47.1, JP47.11, S12.1, U34.10, U35.2, U36.6, U36.16, X12.GND
GND12: C73.C, C74.2, C75.2, C76.2, C77.2, C78.2, D50.C, D52.C, JP51.1, JP51.11, S13.1, U37.10, U38.2, U39.6, U39.16, X13.GND
GND13: C79.C, C80.2, C81.2, C82.2, C83.2, C84.2, D54.C, D56.C, JP55.1, JP55.11, S14.1, U40.10, U41.2, U42.6, U42.16, X14.GND
GND14: C85.C, C86.2, C87.2, C88.2, C89.2, C90.2, D58.C, D60.C, JP59.1, JP59.11, S15.1, U43.10, U44.2, U45.6, U45.16, X15.GND
GND15: C91.C, C92.2, C93.2, C94.2, C95.2, C96.2, D62.C, D64.C, JP63.1, JP63.11, S16.1, U46.10, U47.2, U48.6, U48.16, X16.GND
GND16: C97.C, C98.2, C99.2, C100.2, C101.2, C102.2, D66.C, D68.C, JP67.1, JP67.11, S17.1, U49.10, U50.2, U51.6, U51.16, X17.GND
GND17: C103.C, C104.2, C105.2, C106.2, C107.2, C108.2, D70.C, D72.C, JP71.1, JP71.11, S18.1, U52.10, U53.2, U54.6, U54.16, X18.GND
GND18: C109.C, C110.2, C111.2, C112.2, C113.2, C114.2, D74.C, D76.C, JP75.1, JP75.11, S19.1, U55.10, U56.2, U57.6, U57.16, X19.GND
GND19: C115.C, C116.2, C117.2, C118.2, C119.2, C120.2, D78.C, D80.C, JP79.1, JP79.11, S20.1, U58.10, U59.2, U60.6, U60.16, X20.GND
GND20: C121.C, C122.2, C123.2, C124.2, C125.2, C126.2, D82.C, D84.C, JP83.1, JP83.11, S21.1, U61.10, U62.2, U63.6, U63.16, X21.GND
GND21: C127.C, C128.2, C129.2, C130.2, C131.2, C132.2, D86.C, D88.C, JP87.1, JP87.11, S22.1, U64.10, U65.2, U66.6, U66.16, X22.GND
GND22: C133.C, C134.2, C135.2, C136.2, C137.2, C138.2, D90.C, D92.C, JP91.1, JP91.11, S23.1, U67.10, U68.2, U69.6, U69.16, X23.GND
GND23: C139.C, C140.2, C141.2, C142.2, C143.2, C144.2, D94.C, D96.C, JP95.1, JP95.11, S24.1, U70.10, U71.2, U72.6, U72.16, X24.GND
GND24: C145.C, C146.2, C147.2, C148.2, C149.2, C150.2, D98.C, D100.C, JP99.1, JP99.11, S25.1, U73.10, U74.2, U75.6, U75.16, X25.GND
GND25: C151.C, C152.2, C153.2, C154.2, C155.2, C156.2, D102.C, D104.C, JP103.1, JP103.11, S26.1, U76.10, U77.2, U78.6, U78.16, X26.GND
GND26: C157.C, C158.2, C159.2, C160.2, C161.2, C162.2, D106.C, D108.C, JP107.1, JP107.11, S27.1, U79.10, U80.2, U81.6, U81.16, X27.GND
GND27: C163.C, C164.2, C165.2, C166.2, C167.2, C168.2, D110.C, D112.C, JP111.1, JP111.11, S28.1, U82.10, U83.2, U84.6, U84.16, X28.GND
GND28: C169.C, C170.2, C171.2, C172.2, C173.2, C174.2, D114.C, D116.C, JP115.1, JP115.11, S29.1, U85.10, U86.2, U87.6, U87.16, X29.GND
GND29: C175.C, C176.2, C177.2, C178.2, C179.2, C180.2, D118.C, D120.C, JP119.1, JP119.11, S30.1, U88.10, U89.2, U90.6, U90.16, X30.GND
GND30: C181.C, C182.2, C183.2, C184.2, C185.2, C186.2, D122.C, D124.C, JP123.1, JP123.11, S31.1, U91.10, U92.2, U93.6, U93.16, X31.GND
GND31: C187.C, C188.2, C189.2, C190.2, C191.2, C192.2, D126.C, D128.C, JP127.1, JP127.11, S32.1, U94.10, U95.2, U96.6, U96.16, X32.GND
GND32: C193.C, C194.2, C195.2, C196.2, C197.2, C198.2, D130.C, D132.C, JP131.1, JP131.11, S33.1, U97.10, U98.2, U99.6, U99.16, X33.GND
GND33: C199.C, C200.2, C201.2, C202.2, C203.2, C204.2, D134.C, D136.C, JP135.1, JP135.11, S34.1, U100.10, U101.2, U102.6, U102.16, X34.GND
GND34: C205.C, C206.2, C207.2, C208.2, C209.2, C210.2, D138.C, D140.C, JP139.1, JP139.11, S35.1, U103.10, U104.2, U105.6, U105.16, X35.GND
GND35: C211.C, C212.2, C213.2, C214.2, C215.2, C216.2, D142.C, D144.C, JP143.1, JP143.11, S36.1, U106.10, U107.2, U108.6, U108.16, X36.GND
unnamed: D1.A, R4.2
unnamed: D4.A, R7.1
unnamed: C3.1, R5.1, X1.D+
unnamed: D3.A, R8.2
unnamed: C4.1, R2.1, X1.D-
unnamed: D3.C, U4.17
unnamed: R5.2, U4.11
unnamed: R2.2, U4.12
unnamed: R7.2, SJ1.2
unnamed: D6.A, R9.1
unnamed: D5.A, R11.2
unnamed: D7.A, R12.2
unnamed: D8.A, R10.1
unnamed: D7.C, U6.17
unnamed: C8.1, R3.1, X2.D+
unnamed: C9.1, R1.1, X2.D-
unnamed: R3.2, U6.11
unnamed: R1.2, U6.12
unnamed: R10.2, SJ5.2
unnamed: D10.A, R15.1
unnamed: D9.A, R17.2
unnamed: D11.A, R18.2
unnamed: D12.A, R16.1
unnamed: D11.C, U9.17
unnamed: C14.1, R14.1, X3.D+
unnamed: C15.1, R13.1, X3.D-
unnamed: R14.2, U9.11
unnamed: R13.2, U9.12
unnamed: R16.2, SJ9.2
unnamed: D14.A, R21.1
unnamed: D13.A, R23.2
unnamed: D15.A, R24.2
unnamed: D16.A, R22.1
unnamed: D15.C, U12.17
unnamed: C20.1, R20.1, X4.D+
unnamed: C21.1, R19.1, X4.D-
unnamed: R20.2, U12.11
unnamed: D2.A, R6.1
unnamed: R19.2, U12.12
unnamed: R22.2, SJ13.2
unnamed: D18.A, R27.1
unnamed: D17.A, R29.2
unnamed: D19.A, R30.2
unnamed: D20.A, R28.1
unnamed: D19.C, U15.17
unnamed: C26.1, R26.1, X5.D+
unnamed: C27.1, R25.1, X5.D-
unnamed: R26.2, U15.11
unnamed: R25.2, U15.12
unnamed: R28.2, SJ17.2
unnamed: D22.A, R33.1
unnamed: D21.A, R35.2
unnamed: D23.A, R36.2
unnamed: D24.A, R34.1
unnamed: D23.C, U18.17
unnamed: C32.1, R32.1, X6.D+
unnamed: C33.1, R31.1, X6.D-
unnamed: R32.2, U18.11
unnamed: R31.2, U18.12
unnamed: R34.2, SJ21.2
unnamed: D26.A, R39.1
unnamed: D25.A, R41.2
unnamed: D27.A, R42.2
unnamed: D28.A, R40.1
unnamed: D27.C, U21.17
unnamed: C38.1, R38.1, X7.D+
unnamed: C39.1, R37.1, X7.D-
unnamed: R38.2, U21.11
unnamed: R37.2, U21.12
unnamed: R40.2, SJ25.2
unnamed: D30.A, R45.1
unnamed: D29.A, R47.2
unnamed: D31.A, R48.2
unnamed: D32.A, R46.1
unnamed: D31.C, U24.17
unnamed: C44.1, R44.1, X8.D+
unnamed: C45.1, R43.1, X8.D-
unnamed: R44.2, U24.11
unnamed: R43.2, U24.12
unnamed: R46.2, SJ29.2
unnamed: D34.A, R51.1
unnamed: D33.A, R53.2
unnamed: D35.A, R54.2
unnamed: D36.A, R52.1
unnamed: D35.C, U27.17
unnamed: C50.1, R50.1, X9.D+
unnamed: C51.1, R49.1, X9.D-
unnamed: R50.2, U27.11
unnamed: R49.2, U27.12
unnamed: R52.2, SJ33.2
unnamed: D38.A, R57.1
unnamed: D37.A, R59.2
unnamed: D39.A, R60.2
unnamed: D40.A, R58.1
unnamed: D39.C, U30.17
unnamed: C56.1, R56.1, X10.D+
unnamed: C57.1, R55.1, X10.D-
unnamed: R56.2, U30.11
unnamed: R55.2, U30.12
unnamed: R58.2, SJ37.2
unnamed: D42.A, R63.1
unnamed: D41.A, R65.2
unnamed: D43.A, R66.2
unnamed: D44.A, R64.1
unnamed: D43.C, U33.17
unnamed: C62.1, R62.1, X11.D+
unnamed: C63.1, R61.1, X11.D-
unnamed: R62.2, U33.11
unnamed: R61.2, U33.12
unnamed: R64.2, SJ41.2
unnamed: D46.A, R69.1
unnamed: D45.A, R71.2
unnamed: D47.A, R72.2
unnamed: D48.A, R70.1
unnamed: D47.C, U36.17
unnamed: C68.1, R68.1, X12.D+
unnamed: C69.1, R67.1, X12.D-
unnamed: R68.2, U36.11
unnamed: R67.2, U36.12
unnamed: R70.2, SJ45.2
unnamed: D50.A, R75.1
unnamed: D49.A, R77.2
unnamed: D51.A, R78.2
unnamed: D52.A, R76.1
unnamed: D51.C, U39.17
unnamed: C74.1, R74.1, X13.D+
unnamed: C75.1, R73.1, X13.D-
unnamed: R74.2, U39.11
unnamed: R73.2, U39.12
unnamed: R76.2, SJ49.2
unnamed: D54.A, R81.1
unnamed: D53.A, R83.2
unnamed: D55.A, R84.2
unnamed: D56.A, R82.1
unnamed: D55.C, U42.17
unnamed: C80.1, R80.1, X14.D+
unnamed: C81.1, R79.1, X14.D-
unnamed: R80.2, U42.11
unnamed: R79.2, U42.12
unnamed: R82.2, SJ53.2
unnamed: D58.A, R87.1
unnamed: D57.A, R89.2
unnamed: D59.A, R90.2
unnamed: D60.A, R88.1
unnamed: D59.C, U45.17
unnamed: C86.1, R86.1, X15.D+
unnamed: C87.1, R85.1, X15.D-
unnamed: R86.2, U45.11
unnamed: R85.2, U45.12
unnamed: R88.2, SJ57.2
unnamed: D62.A, R93.1
unnamed: D61.A, R95.2
unnamed: D63.A, R96.2
unnamed: D64.A, R94.1
unnamed: D63.C, U48.17
unnamed: C92.1, R92.1, X16.D+
unnamed: C93.1, R91.1, X16.D-
unnamed: R92.2, U48.11
unnamed: R91.2, U48.12
unnamed: R94.2, SJ61.2
unnamed: D66.A, R99.1
unnamed: D65.A, R101.2
unnamed: D67.A, R102.2
unnamed: D68.A, R100.1
unnamed: D67.C, U51.17
unnamed: C98.1, R98.1, X17.D+
unnamed: C99.1, R97.1, X17.D-
unnamed: R98.2, U51.11
unnamed: R97.2, U51.12
unnamed: R100.2, SJ65.2
unnamed: D70.A, R105.1
unnamed: D69.A, R107.2
unnamed: D71.A, R108.2
unnamed: D72.A, R106.1
unnamed: D71.C, U54.17
unnamed: C104.1, R104.1, X18.D+
unnamed: C105.1, R103.1, X18.D-
unnamed: R104.2, U54.11
unnamed: R103.2, U54.12
unnamed: R106.2, SJ69.2
unnamed: D74.A, R111.1
unnamed: D73.A, R113.2
unnamed: D75.A, R114.2
unnamed: D76.A, R112.1
unnamed: D75.C, U57.17
unnamed: C110.1, R110.1, X19.D+
unnamed: C111.1, R109.1, X19.D-
unnamed: R110.2, U57.11
unnamed: R109.2, U57.12
unnamed: R112.2, SJ73.2
unnamed: D78.A, R117.1
unnamed: D77.A, R119.2
unnamed: D79.A, R120.2
unnamed: D80.A, R118.1
unnamed: D79.C, U60.17
unnamed: C116.1, R116.1, X20.D+
unnamed: C117.1, R115.1, X20.D-
unnamed: R116.2, U60.11
unnamed: R115.2, U60.12
unnamed: R118.2, SJ77.2
unnamed: D82.A, R123.1
unnamed: D81.A, R125.2
unnamed: D83.A, R126.2
unnamed: D84.A, R124.1
unnamed: D83.C, U63.17
unnamed: C122.1, R122.1, X21.D+
unnamed: C123.1, R121.1, X21.D-
unnamed: R122.2, U63.11
unnamed: R121.2, U63.12
unnamed: R124.2, SJ81.2
unnamed: D86.A, R129.1
unnamed: D85.A, R131.2
unnamed: D87.A, R132.2
unnamed: D88.A, R130.1
unnamed: D87.C, U66.17
unnamed: C128.1, R128.1, X22.D+
unnamed: C129.1, R127.1, X22.D-
unnamed: R128.2, U66.11
unnamed: R127.2, U66.12
unnamed: R130.2, SJ85.2
unnamed: D90.A, R135.1
unnamed: D89.A, R137.2
unnamed: D91.A, R138.2
unnamed: D92.A, R136.1
unnamed: D91.C, U69.17
unnamed: C134.1, R134.1, X23.D+
unnamed: C135.1, R133.1, X23.D-
unnamed: R134.2, U69.11
unnamed: R133.2, U69.12
unnamed: R136.2, SJ89.2
unnamed: D94.A, R141.1
unnamed: D93.A, R143.2
unnamed: D95.A, R144.2
unnamed: D96.A, R142.1
unnamed: D95.C, U72.17
unnamed: C140.1, R140.1, X24.D+
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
